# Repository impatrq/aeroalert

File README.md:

<div align="center">

# **AeroAlert**

</div>

# ¿Qué es AeroAlert?

Aeroalert es un prototipo de sistema de emergencia para aeronaves basado en el monitoreo constante de parámetros de salud de los pilotos para prevenir accidentes aeronauticos.
El sistema cuenta con una pulsera dotada de los sensores necesarios. Si se detecta un estado de salud urgente que implique que el piloto este incapaz de controlar la aeronave, se le otorga el control al piloto automático nativo, el cual, a través de dos equipos de procesamiento diseñados por nosotros, entabla una comunicación con la CTRT correspondiente para llevar la aeronave a una situación que permita evitar el riesgo de accidente.

 * 🎞️​ Video presentación: [Aeroalert](https://www.youtube.com/watch?v=lwCH7T5NRF8&ab_channel=ProyectoAeroAlert)

 * 📰 [Notas y difusión](https://docs.google.com/document/d/1UdKEXQvbZDQbbGeclpEPnfsf2L1TE1_X/edit?usp=sharing&ouid=106181145058354130516&rtpof=true&sd=true)

### ¿Quiénes lo desarrollan?
AeroAlert es un proyecto realizado por alumnos de 7mo Año de la **Escuela de Educación Secundaria Técnica N°7 "Taller Regional Quilmes"**, especialidad Aviónica.

# Integrantes

 * ### *Altinier, Mauro*

    *    📷 Instagram: [@agustin_altinier](https://www.instagram.com/agustin_altinier/)
    *    📧 Email: [mauro.altinier@gmail.com](mailto:mauro.altinier@gmail.com)         
    *     LinkedIn: [Mauro-Agustin-Altinier](https://www.linkedin.com/in/Mauro-Agustín-Altinier)

 * ###  *Cuccaro, Juan*

    *    📷 Instagram: [@cuccaro_juan](https://www.instagram.com/cuccaro_juan/)
    *    📧 Email: [manucucca10@gmail.com](mailto:manucucca10@gmail.com)
    *     LinkedIn: [juan-cuccaro](https://www.linkedin.com/in/juan-cuccaro/)

 * ###  *Husulak, Mateo*

    *    📷 Instagram: [@matehusu_2](https://www.instagram.com/matehusu_2/)
    *    📧 Email: [matehusu@gmail.com](mailto:matehusu@gmail.com)
    *     LinkedIn: [mateo-gaston-husulak-ledo](https://www.linkedin.com/in/mateo-gaston-husulak-ledo-52b742270/)

 * ###  *López, Teo*

    *    🧾​ Curriculum vitae: [CVLópezTeoNicolas](https://drive.google.com/file/d/1_G5UPTjoewlIe7h19vwuFQ2f_dssRR7e/view?usp=sharing)
    *    📷 Instagram: [@nico67676](https://www.instagram.com/nico67676/)
    *    📧 Email: [teonicolaslopez8@gmail.com](mailto:teonicolaslopez8@gmail.com)
    *     LinkedIn: [teo-lópez](https://www.linkedin.com/in/teo-lópez/)

 * ###  *Pagano, Jonás*

    *    📷 Instagram: [@jonaspagano](https://www.instagram.com/jonaspagano/)
    *    📧 Email: [paganojonas@gmail.com](mailto:paganojonas@gmail.com)
    *     LinkedIn: [jonaspagano](https://www.linkedin.com/in/jonaspagano/)

 * ###  *Roca, Leandro*

    *    📷 Instagram: [@lean_ro64](https://www.instagram.com/lean_ro64/)
    *    📧 Email: [leandroroca49@gmail.com](mailto:leandroroca49@gmail.com)
    *     LinkedIn: [leandro-roca](https://www.linkedin.com/in/leandro-roca/)

 * ###  *Ruíz, Nicolás*
    *    📷 Instagram: [@nicoo__ruiz](https://www.instagram.com/nicoo__ruiz/)
    *    📧 Email: [ruizagustinnicolas20@gmail.com](mailto:ruizagustinnicolas20@gmail.com)
    *     LinkedIn: 

# **Contactos** 

* ####    📧 Email: [proyectoaeroalert@gmail.com](mailto:proyectoaeroalert@gmail.com)
* ####    🌐 Página Web: [www.aeroalert.com.ar](https://www.aeroalert.com.ar/)
* ####    📷 Instagram: [@aeroalert.impa](https://www.instagram.com/aeroalert.impa/)
* ####     LinkedIn: [AeroAlert](https://www.linkedin.com/company/aeroalert/)

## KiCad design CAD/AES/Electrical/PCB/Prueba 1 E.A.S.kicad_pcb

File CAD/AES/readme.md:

<div align="left">

# **Automatic Emergency System (AES)**
Acrónimo en idioma inglés de Automatic Emergency System, es el módulo que se se encuentra alojado en cabina, encargado de recibir y procesar la información recopilada por la instrumentación sensorial del sistema (módulo V.D.B). Este equipo desempeña un papel crucial al emitir avisos pertinentes en cabina, establecer comunicación con el equipo en tierra y, en situaciones críticas, interactuar con el piloto automático nativo de la aeronave. La capacidad de establecer comunicación bidireccional con el equipo en tierra permite la transmisión efectiva de datos relevantes y la recepción de instrucciones actualizadas, lo cual es esencial para la coordinación durante operaciones de emergencia.

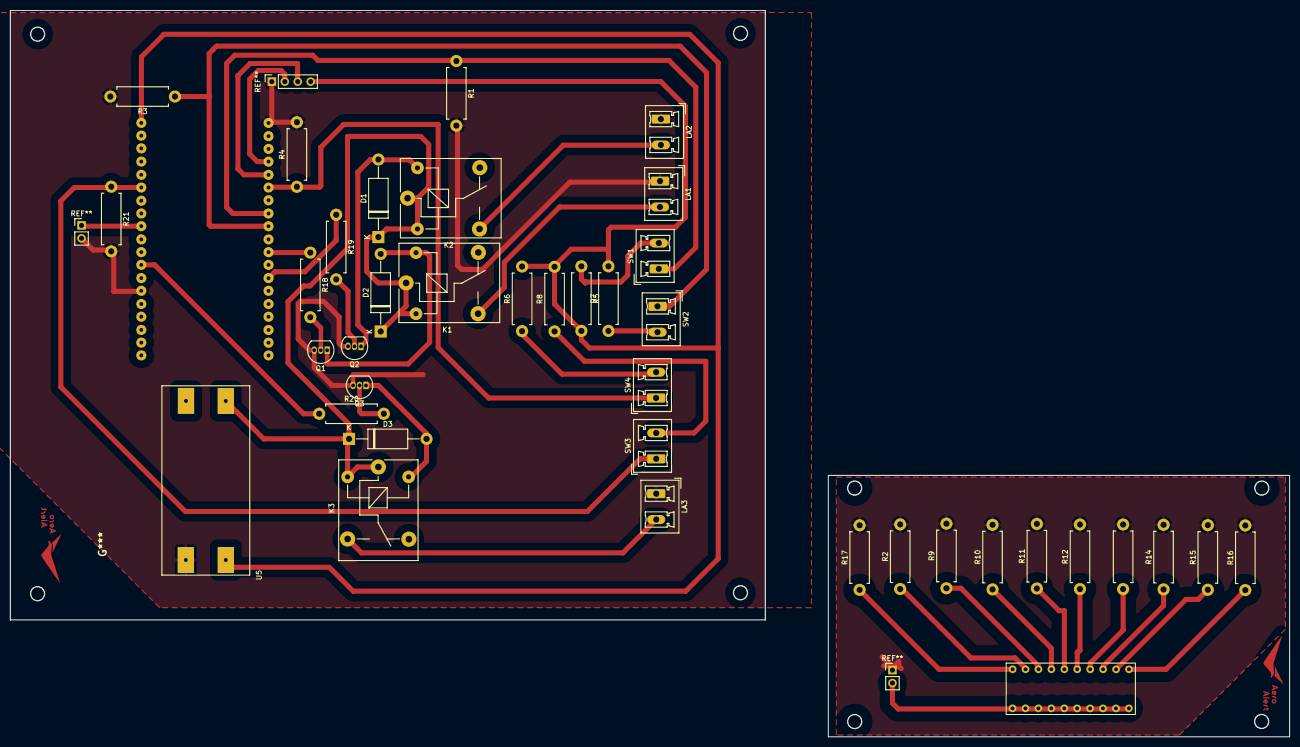
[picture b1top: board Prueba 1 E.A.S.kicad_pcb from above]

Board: 2 copper layers, 251.5 x 142.8 mm, 40 parts (0 on the bottom side), 34 nets.

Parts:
BAR1: HDSP-4830_2; Led Bar Display
D1, D2, D3: D; D_DO-15_P15.24mm_Horizontal
K1, K2, K3: ADW11; Relay_SPDT_SANYOU_SRD_Series_Form_C
LA1: Alert; PhoenixContact_MCV_1,5_2-G-5.08_1x02_P5.08mm_Vertical
LA2: Warning; PhoenixContact_MCV_1,5_2-G-5.08_1x02_P5.08mm_Vertical
LA3: Test Fail; PhoenixContact_MCV_1,5_2-G-5.08_1x02_P5.08mm_Vertical
Q1, Q2, Q3: BC337; TO-92_Inline
R1, R2, R3, R4, R5, R6, R7, R8, R9, R10, R11, R12, R13, R14, R15, R16, R17, R18, R19, R20, R21: R; R_Axial_DIN0411_L9.9mm_D3.6mm_P12.70mm_Horizontal
SW1: Reaction; PhoenixContact_MCV_1,5_2-G-5.08_1x02_P5.08mm_Vertical
SW2: Test; PhoenixContact_MCV_1,5_2-G-5.08_1x02_P5.08mm_Vertical
SW3: Keylock (On/Off); PhoenixContact_MCV_1,5_2-G-5.08_1x02_P5.08mm_Vertical
SW4: Manual; PhoenixContact_MCV_1,5_2-G-5.08_1x02_P5.08mm_Vertical
U1: ESP32-WROOM-32; ESP32 NODEMCU
U5: Entrada 12V; MT 3608

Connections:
3V3: R5.2, R6.2, R7.2, R8.2, U1.1 (GND), U5.1 (Vin+)
12V: D1.1 (K), D2.1 (K), D3.1 (K), K1.1, K1.2, K2.1, K2.2, K3.1, K3.2, U5.3 (Vout+)
A: BAR1.1 (A), BAR1.2 (A), BAR1.3 (A), BAR1.4 (A), BAR1.5 (A), BAR1.6 (A), BAR1.7 (A), BAR1.8 (A), BAR1.9 (A), BAR1.10 (A), U1.10 (IO25)
FAIL: R20.1, U1.13 (IO14)
GNDREF: LA1.1 (-), LA2.1 (-), LA3.1 (-), Q1.3 (E), Q2.3 (E), Q3.3 (E), R1.2, R2.2, R3.2, R4.2, R9.2, R10.2, R11.2, R12.2, R13.2, R14.2, R15.2, R16.2, R17.2, R21.2, U1.2 (VDD), U1.15 (GND), U5.2 (Vin-)
unnamed: BAR1.11 (K), R16.1
unnamed: BAR1.12 (K), R15.1
unnamed: BAR1.13 (K), R14.1
unnamed: BAR1.14 (K), R13.1
unnamed: BAR1.15 (K), R12.1
unnamed: BAR1.16 (K), R11.1
unnamed: BAR1.17 (K), R10.1
unnamed: BAR1.18 (K), R9.1
unnamed: BAR1.19 (K), R2.1
unnamed: BAR1.20 (K), R17.1
unnamed: D1.2 (A), K2.5, Q2.1 (C)
unnamed: D2.2 (A), K1.5, Q1.1 (C)
unnamed: D3.2 (A), K3.5, Q3.1 (C)
unnamed: K1.3, LA1.2 (+)
unnamed: K2.3, LA2.2 (+)
unnamed: K3.3, LA3.2 (+)
unnamed: Q1.2 (B), R18.2
unnamed: Q2.2 (B), R19.2
unnamed: Q3.2 (B), R20.2
unnamed: R5.1, SW1.2
unnamed: R6.1, SW4.2
unnamed: R7.1, SW2.2
unnamed: R21.1, SW3.1 (C), U1.7 (IO35)
unnamed: R8.1, SW3.2 (D)
unnamed: R19.1, U1.31 (IO19)
unnamed: R18.1, U1.29 (IO5)
unnamed: R3.1, SW2.1, U1.27 (IO16)
unnamed: R1.1, SW1.1, U1.26 (IO4)
unnamed: R4.1, SW4.1, U1.24 (IO2)

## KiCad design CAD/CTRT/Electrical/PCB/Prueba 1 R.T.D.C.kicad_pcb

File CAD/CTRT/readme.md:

<div align="left">

# **Control Tower Reciever - Transmitter (CTRT)**
Acrónimo en idioma inglés alusivo a Control Tower Reciever and Transmitter (en español: Receptor y Transmisor de la Torre de Control), es un módulo alojado en tierra y a disposición del control de tráfico aéreo, cuyo propósito es el de recibir, representar visualmente e informar a los controladores aéreos de emergencias, alertas y/o peticiones. Además de su rol informativo, el módulo C.T.R.T se encarga de generar y transmitir instrucciones al equipo en cabina, específicamente al módulo A.E.S. Su propósito primordial es facilitar la ejecución de aterrizajes de emergencia en caso de que esta acción sea necesaria, garantizando una comunicación efectiva y coordinada entre la torre de control y la aeronave, contribuyendo así a la seguridad y eficiencia en situaciones críticas.

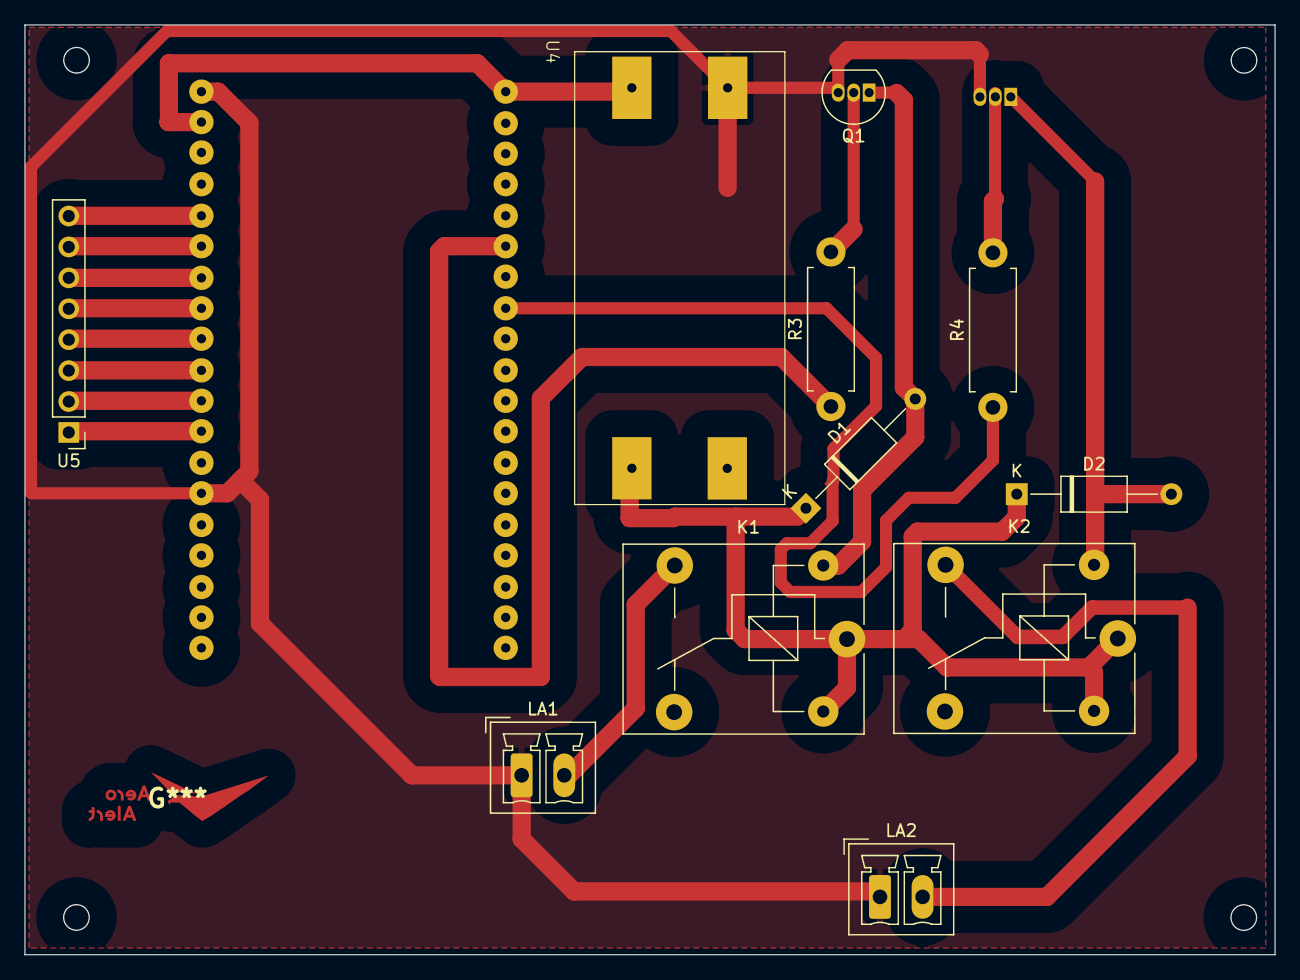
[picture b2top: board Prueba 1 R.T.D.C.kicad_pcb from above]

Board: 2 copper layers, 102.7 x 76.4 mm, 13 parts (1 on the bottom side), 19 nets.

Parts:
D1, D2: D; D_A-405_P12.70mm_Horizontal
K1, K2: ADW11; Relay_SPDT_SANYOU_SRD_Series_Form_C
LA1: Alert; PhoenixContact_MCV_1,5_2-G-3.5_1x02_P3.50mm_Vertical
LA2: Warning; PhoenixContact_MCV_1,5_2-G-3.5_1x02_P3.50mm_Vertical
Q1, Q2: BC337; TO-92_Inline
R3, R4: 10K; R_Axial_DIN0411_L9.9mm_D3.6mm_P12.70mm_Horizontal
U1: ESP32-WROOM-32; ESP32 NODEMCU
U4: Entrada 12V; MT 3608
U5: PinHeader_1x08_P2.54mm_Vertical

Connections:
1: U1.13 (IO14), U5.1 (C4)
2: U1.12 (IO27), U5.2 (C3)
3: U1.11 (IO26), U5.3 (C2)
3V3: U1.2 (VDD), U1.3 (EN), U4.1 (Vin+)
4: U1.10 (IO25), U5.4 (C1)
5: U1.9 (IO33), U5.5 (R4)
6: U1.8 (IO32), U5.6 (R3)
7: U1.7 (IO35), U5.7 (R2)
8: U1.6 (IO34), U5.8 (R1)
12V: D1.1 (K), D2.1 (K), K1.1, K1.3, K2.1, K2.3, U4.3 (Vout+)
GNDREF: LA1.1 (-), LA2.1 (-), Q1.3 (E), Q2.3 (E), U1.1 (GND), U1.15 (GND), U4.2 (Vin-)
IO4: R4.1, U1.26 (IO4)
unnamed: D1.2 (A), K1.2, Q1.1 (C)
unnamed: D2.2 (A), K2.6, Q2.1 (C)
unnamed: K1.5, LA1.2 (+)
unnamed: K2.5, LA2.2 (+)
unnamed: Q1.2 (B), R3.2
unnamed: Q2.2 (B), R4.2
unnamed: R3.1, U1.24 (IO2)

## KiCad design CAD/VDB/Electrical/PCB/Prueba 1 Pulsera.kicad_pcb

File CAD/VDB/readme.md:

<div align="left">

# **Vital Data Bracelet (VDB)**
Acrónimo en idioma inglés de Vital Data Bracelet (en español: Pulsera Detectora de Signos Vitales), corresponde al dispositivo pulsera portado tanto por piloto como por copiloto (en caso de existir este último). Su función principal es aquella relacionada al relevamiento de datos asociados a la salud de los conductores de la aeronave (llámese comandante y su potencial compañero de fórmula en caso de existir), con el objetivo de proveer un monitoreo permanente de las variables a medir tanto en cabina como en tierra, de forma tal que exista la posibilidad de generar alertas y/o emergencias tanto de manera presencial (en el medio de transporte físico del vuelo) como remota (por medio del control de tráfico aéreo) en función de las variables de salud relevadas por el módulo descrito previamente, permitiendo la detección temprana de posibles problemas de salud y la toma de medidas adecuadas. La integración de esta tecnología se alinea con el enfoque del proyecto para garantizar la monitorización efectiva de los signos vitales y la rápida respuesta ante cualquier eventualidad.

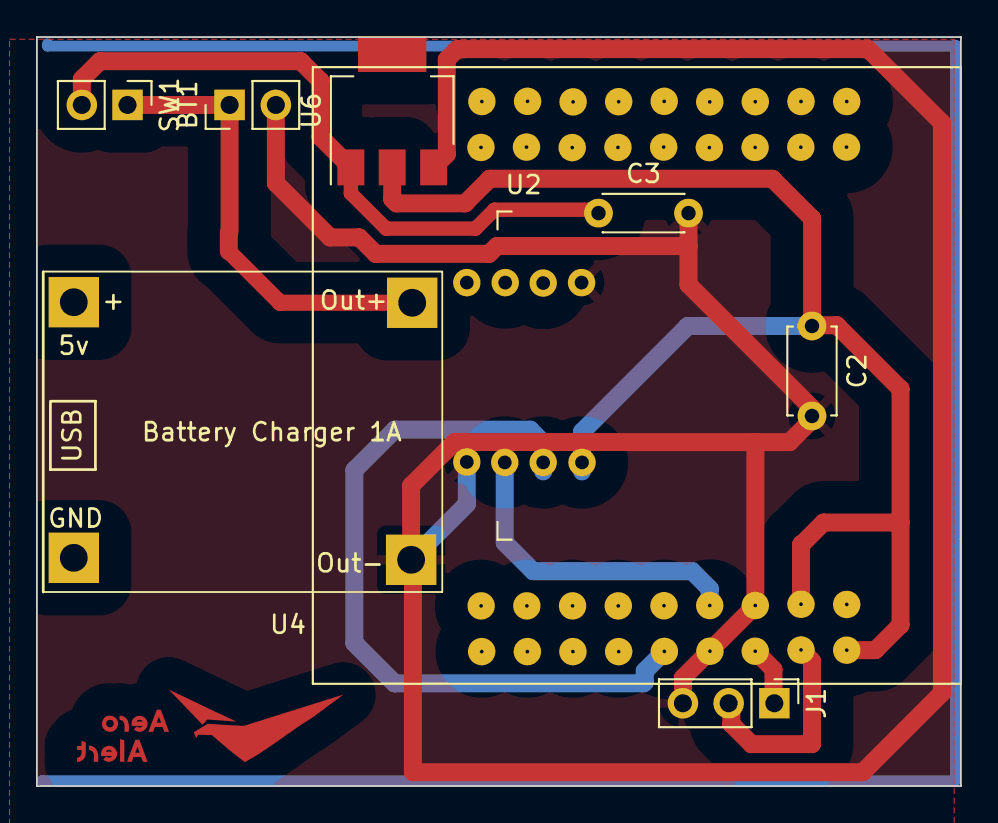
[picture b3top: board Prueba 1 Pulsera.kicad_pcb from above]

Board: 2 copper layers, 51.3 x 41.6 mm, 9 parts (1 on the bottom side), 8 nets.

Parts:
BT1: 3.7V; PinHeader_1x02_P2.54mm_Vertical
C2: 10u; C_Disc_D4.7mm_W2.5mm_P5.00mm
C3: 10u; C_Disc_D4.3mm_W1.9mm_P5.00mm
J1: Conn_01x03_Socket; PinHeader_1x03_P2.54mm_Vertical
SW1: SW_DIP_x01; PinHeader_1x02_P2.54mm_Vertical
U1: MAX30102
U2: ESP32-WROOM-32
U4: TP4056; TP4056-18650
U6: LM1117DT-3.3; SOT-223

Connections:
GNDREF: BT1.2 (-), C2.2, C3.2, J1.3, U1.4 (PGND), U1.12 (GND), U1.13 (~INT), U2.1 (GND), U2.37 (IO23), U2.38 (GND), U4.4 (OUT-), U6.3 (VI)
unnamed: J1.1, U2.35 (TXD0/IO1)
unnamed: J1.2, U2.34 (RXD0/IO3)
unnamed: C3.1, SW1.2, U6.1 (GND)
PWR: BT1.1 (+), SW1.1, U4.3 (OUT+)
SCK: U1.2 (SCL), U2.36 (IO22)
SDA: U1.3 (SDA), U2.33 (IO21)
VDD: C2.1, U1.11 (VDD), U2.2 (VDD), U2.3 (EN), U6.2 (VO)

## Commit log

2023-05-05 docs: agregar nombre
2023-05-05 docs: agregar imagen
2023-05-05 Actualizar README.md
2023-05-05 docs: cambiar ordenes nombres
2023-05-05 docs: Añadir descripción del proyecto
2023-05-05 docs: Cambios menores en información
2023-05-05 docs: Cambio menor al diagramado del documento
2023-05-05 docs: Corrección de cambio hecho previamente al documento
2023-05-09 feat: add wifi programs band/pae
2023-05-09 docs: create folder wifi
2023-05-09 docs: crear subcarpetas
2023-05-09 chore: add programs sensor esp32
2023-05-09 docs: add documentacion max30102
    docs: datasheet sensor
    docs: datasheet infrarrojo
    docs: oximetria
2023-05-10 feat: station send data to accespoint (v2)
2023-05-10 fix: masomenos wifi
2023-05-12 feat: add important data send
    pasa bpm
2023-05-12 chore: adjust time
    se trababa por imprimir mucho "not finger"
2023-05-12 feat: send in json and asign in variables
2023-05-12 chore: borrar algo
2023-05-15 feat: mide temperatura
2023-05-16 style: sensar temperatura comentado
2023-05-16 perf: declarar variables 1 sola vez
2023-05-16 style: ordenar
2023-05-16 feat: comunicacion bidireccional doble comentado
2023-05-16 style: separar respuestas
2023-05-16 feat: enviar respuesta post-recepcion
2023-05-16 feat: comunicacion bidireccional y opciones
2023-05-16 refactor: cambiar import station para mantenerlo
2023-05-19 feat: comunicar 2 station 1 access point
2023-05-29 feat: web-page
2023-05-29 feat: evaluar datos y ordenado
2023-06-01 feat: agregar protocolos
2023-06-05 docs: diagrama Sae
2023-06-05 me confundi
2023-06-05 docs: diagrama Sae protocolos
2023-06-21 feat: add protocols
2023-06-21 fix: conexion wifi
2023-07-11 feat: .py prueba de sensor
    principal: archivo a continuar desarrollando
2023-07-11 fix: cant stop esp32 mini when program uploaded
2023-07-11 refactor: for testing
2023-07-11 style: remove useless things
2023-07-11 feat: testing communication
2023-08-01 rename
2023-08-01 sorting things
2023-08-01 fixing
2023-08-04 actividad fabri microdot
2023-08-04 stations
2023-08-04 fix: correcciones wifi
2023-08-08 wifi working perfectly with sensor and sae
2023-08-11 envio de datos, r4ecepcion y casos masomenos
2023-08-15 fixed errors sae
2023-08-15 comentado: Protocolos sae
2023-08-16 feat swithces de prueba copiloto
2023-08-25 Sae optimized
2023-08-28 optimize and order
2023-08-28 feat: uart
2023-08-31 perf: optimize repeated code
2023-09-03 new version
2023-09-18 probar uart
2023-09-28 rtdc wifi connection
2023-10-03 wifi con rtdc funciona
2023-10-04 HU07A1: implementacion prendido con boton
2023-10-04 refactor
2023-10-04 feat: wifi pc
2023-10-04 feat: filtrar mensajes
2023-10-04 wifi plus arcade
2023-10-04 feat: GUI
2023-10-08 fix: receive info PC and analyze
2023-10-09 feat: use info from PC switches
2023-10-09 feat: request landing information
2023-10-10 fix: pc info usage
2023-10-12 fix: protocols
2023-10-14 Add files via upload
    Xplane Safe Return Emergency AutoLand (FlyWithLua)
2023-10-15 sort files and code
2023-10-16 feat: CTRT processing
2023-10-17 refactor: images in folder
2023-10-17 style: clear blank spaces
2023-10-17 edit gitignore
2023-10-17 feat: enviar info aeropuerto al solicitarse
2023-10-17 feat: gestion web_page
2023-10-17 feat: manage alerts web_page
2023-10-18 feat: manage multiple flights
2023-10-18 feat: send airport for landing
2023-10-18 style
2023-10-18 docs: create folder documentacion
2023-10-18 rename folder
2023-10-18 feat: diccionario para tabla de vuelos
2023-10-18 fix: diccionario para lista de vuelos
2023-10-19 refactor: diccionario_vuelos
2023-10-20 change directory and style
2023-10-20 process info in web page
2023-10-20 feat: iterate json info in page
2023-10-20 Cambios en caps deploying y corte de suministro de combustible.
2023-10-21 feat: keys web page
2023-10-21 fix: band not finger constantly
2023-10-21 feat: calibration for bpm
2023-10-22 Modificar activación de vertical speed y condición de approach
2023-10-22 fix: max30102 calibration bpms
2023-10-22 finish: backend CTRT
2023-10-23 feat: ctrt boceto y js
2023-10-23 feat: create table and update info
2023-10-23 feat: add to js code
2023-10-23 feat: web page flight history table
2023-10-23 feat: max history to data in web page
2023-10-24 feat: create table airports
2023-10-24 feat: sound, selector and change table
2023-10-24 Modificar curso de referencia (en grados) para aproximación
2023-10-24 testing phase
2023-10-24 feat: aes sound alarms
2023-10-24 more alerts
2023-10-24 test and more alerts
2023-10-24 fix: band wifi
2023-10-24 cosas
2023-10-25 fix: ctrt tables not creating
2023-10-25 feat: Simulador recibe instrucciones Aes
2023-10-25 feat: playing alerts
2023-10-25 style: prueba-sonido sleeps
2023-10-26 feat: new version protocols testing
2023-10-26 feat: new version protocols lights
2023-10-26 feat: mas de los protocolos ayuda tengo sueño
2023-10-26 style: remove unnecessary code
2023-10-30 testing CTRT
2023-10-31 fixs
2023-10-31 fix: length not function
2023-10-31 style tabs
2023-11-01 fix: history not working
2023-11-01 fix: keys working
2023-11-02 feat: ctrt interface working
2023-11-04 Optimizar fase de aterrizaje
2023-11-04 Fase de aterrizaje optimizada
2023-11-06 clean folders
2023-11-07 feat: send alerts to pc
2023-11-09 feat: band working
2023-11-09 feat: all alerts working in ctrt and aes + communication
2023-11-10 change folders
2023-11-10 clean and rename folders
2023-11-10 feat: more delay
2023-11-10 feat: change controls
2023-11-15 Documentación actualizada a la fecha (15/11/2023)
2023-11-15 Modelado 3D, ensamblaje y vista explotada (VDB)
2023-11-15 Modelado 3D, Ensamblaje y Vista Explotada (AES)
2023-11-15 Modelado 3D, Ensamblaje y Vista Explotada (CTRT)
2023-11-15 Archivos de Esquemático, PCB, PDF para impresión
2023-11-15 Archivos de Esquemático, PCB, PDF para impresión
2023-11-15 Logotipos de marca
2023-11-15 Letras del logotipo
2023-11-15 Disposiciones alternativas del logitpo
2023-11-15 Banner para exposición del proyecto
2023-11-15 Recursos adicionales para banners y documentación
2023-11-15 Plano acotado VDB
2023-11-15 Planos acotados CTRT
2023-11-15 Planos acotados AES
2023-11-17 feat: utilizar barras piloto 2
2023-11-17 crear carpeta Imagenes
2023-11-17 add photos and try sizes
2023-11-17 size and circle images
2023-11-17 create readme pc-xplane
2023-11-17 saque una "de"
2023-11-17 arregle en lo que me equivoque
2023-11-17 Corrección de mis redes
2023-11-17 arreglar explicacion readme
2023-11-17 Cambios del orden de documentación
    Cambio dentro del orden de los documentos, se creo dos carpetas una relacionada los documentos del prototipo y otra relacionada a los documentos del funcionamiento en la aviación
2023-11-17 Create Readme.md VDB
2023-11-17 Docs: Agregar documentos faltantes
    Faltaban 2 documentos: Anteproyecto y Manual de Usuario
2023-11-17 Docs: Documentos faltantes del Funcionamientos en la Aviación
    Terminar de actualizar la ducumentación del proyecto
2023-11-17 Docs: Corrección de ortografía
    Corrección ortografía de los titulos de los documentos
2023-11-17 chore: Comentar UART_X-Plane
2023-11-18 Archivo .step PCB A.E.S
2023-11-18 Archivo .step PCB C.T.R.T
2023-11-18 Archivo .setp PCB V.D.B
2023-11-18 Archivo .step PCB V.D.B
2023-11-18 Sized photos
2023-11-18 AeroAlert Logotipo Completo (Transparente)
2023-11-18 Solicitud de Materiales
2023-11-18 feat: change folder name
2023-11-19 feat: nueva carpeta y traslado de archivos
2023-11-19 Facturación de Compras
2023-11-19 Agregado del documento "Administración de presupuesto"
2023-11-19 Curriculum López Teo
2023-11-19 Corrección de CV
2023-11-19 Video presentación
2023-11-21 Comentarios: Aes Acessv9.py
2023-11-21 Certificados de participación (Pagano y Ruiz)
2023-11-21 Iconos para historias destacadas
2023-11-21 Actualización de planilla de compras
2023-11-21 Corrección
2023-11-22 Docs: Subir Certificado Oniet
    Subo el certificado de Oniet
2023-11-22 Cambio README.md
    El README tenia los punto mal puestos
2023-11-22 Chore: Code commented Accessv9.py
    Comente parte del codigo
2023-11-22 Docs: Presentación de Ventas (Entrepiso)
2023-11-22 Elementos de alcances inconclusos
2023-11-22 Fotos de AES y CTRT
2023-11-22 Explicación del A.E.S
2023-11-22 Explicación CTRT
2023-11-22 QR de Difusión
2023-11-22 Agregado de certificado ONIET
2023-11-22 Readme
2023-11-22 VDB explicación
2023-11-23 chore: Comentar GUI
2023-11-23 Docs: Manual de Usuario Actualizado
2023-11-23 Docs: Arreglo de links a redes profesionales defectuosos
2023-11-23 add Index and created folder on Web page
2023-11-23 add index.css and created folder on "css"
2023-11-23 add scripts-Inicio.js and created folder on Web page named "script"
2023-11-23 Add "script2.js"
2023-11-23 Create a folder "htmls" and add de file "Acercade.html"
2023-11-23 Create "Nosotros.html"
2023-11-23 Add "Nosotros.css"
2023-11-23 Create "Contacto.html"
2023-11-23 Add "Contacto.css"
2023-11-23 Add all files about Boostrap
2023-11-23 Create folder "CV Personales" and I added everyone's CV
2023-11-23 Create folder "Documentos" and I added our documentation
2023-11-23 I created the img folder and added all the images that we used to create the website
2023-11-23 Add the file "CNAME"
2023-11-23 Create a README.md and this is the first tried
2023-11-23 I am so stupid and confused the link from my website
2023-11-23 Add LinkedIn and change the words
2023-11-23 Add Gmail
2023-11-23 Tried with Readme
2023-11-23 The last tried failed
2023-11-23 Readme.md changes
2023-11-23 Change Name
2023-11-23 resubida de archivos
2023-11-24 resubida de archivos CTRT
2023-11-24 resubida de archivos AES
2023-11-24 Update .gitignore
    .DS_Store in main
2023-11-24 agregué mi linkedin
2023-11-24 agregar nombre completo bien
2023-11-24 Comentado del 25% del codigo
2023-11-24 Codigo comentado al 50% del AES accesv9
2023-11-24 Codigo comentado del accessv9 al 75%
2023-11-24 Comentado del codigo del AES accessv9 terminado
2023-11-24 Aes main.py comentado al 100%
2023-11-24 test
2023-11-24 move folder
2023-11-24 Revert "test"
    This reverts commit 75337bd3fbc72137d0644d74614b593ee438620f.
2023-11-24 change file name
2023-11-24 change folder again not working
2023-11-24 Comentarios 25% Codigo CTRT.PY
2023-11-24 Codigo CTRT.py 100% comentadado
2023-11-24 remove useless microdot_asyncio
2023-11-24 chore: remove files uploaded wrongly
2023-11-24 style: accessv9
2023-11-24 style: change variable
2023-11-24 Arreglo para que se vea la imagen
2023-11-24 cambiar el codigo
2023-11-24 arreglar codigo
2023-11-24 finalizar codigo
2023-11-28 Docs: Corrección de ruta a imagen grupal
2023-11-28 feat: Archivos .step y .sldprt para ensamblajes
2023-11-29 Docs: Archivos de Routeado CNC (Carcasas AES / CTRT)
